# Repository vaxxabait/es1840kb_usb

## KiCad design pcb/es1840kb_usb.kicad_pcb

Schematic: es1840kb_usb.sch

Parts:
C1: 10 µF
C2, C6: 1 µF
C3, C5: 18 pF
C4: 100 nF
DD1: ATMEGA32U2; TQFP32
HL1, HL2, HL3: LED
R1, R2: 22 Ω
R3, R4, R5: 220 Ω
X1: USB
X2: ISP
X3: OLED
XP1: Keyboard
ZQ1: 16 MHz

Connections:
/DBG_RSTn: DD1.24, X2.5 (~RST)
/KB_COL0: DD1.7, XP1.12 (COL_0)
/KB_COL1: DD1.8, XP1.13 (COL_1)
/KB_COL2: DD1.9, XP1.14 (COL_2)
/KB_COL3: DD1.10, XP1.15 (COL_3)
/KB_COL_EN: DD1.6, XP1.21 (COL_EN)
/KB_DAT: DD1.20, XP1.39 (KEY_IN)
/KB_ROW0: DD1.11, XP1.16 (ROW_0)
/KB_ROW1: DD1.12, XP1.17 (ROW_1)
/KB_ROW2: DD1.13, XP1.18 (ROW_2)
/LED_CAPS: DD1.22, R3.2
/LED_EN: DD1.23, XP1.5 (LED_EN)
/LED_LAT: DD1.26, XP1.33 (LED_LAT)
/LED_NUM: DD1.5, XP1.34 (LED_NUM)
/LED_PWR: HL2.2, R4.1
/LED_RUS: DD1.25, XP1.32 (LED_RUS)
/LED_SCRL: DD1.21, R5.2
/OLED_CSn: DD1.14, X3.7 (~CS)
/OLED_DC: DD1.19, X3.6 (D/~C)
/OLED_RSTn: DD1.18, X3.5 (~RES)
/SPI_CLK: DD1.15, X2.3 (SCLK), X3.3 (SCL/SCLK)
/SPI_MISO: DD1.17, X2.1 (MISO)
/SPI_MOSI: DD1.16, X2.4 (MOSI), X3.4 (SDA/MOSI)
/USB_CAP: C6.1, DD1.27
/USB_N: DD1.30, R2.2
/USB_P: DD1.29, R1.2
/XTAL_N: C5.2, DD1.2, ZQ1.2
/XTAL_P: C3.2, DD1.1, ZQ1.1
DGND: C1.2, C2.2, C3.1, C4.1, C5.1, C6.2, DD1.3, DD1.28, R4.2, X1.4 (GND), X2.6 (GND), X3.1 (GND), XP1.20 (GND)
unnamed: R1.1, X1.3 (D+)
unnamed: HL1.2, R3.1
unnamed: HL3.2, R5.1
unnamed: R2.1, X1.2 (D-)
VCC5: C1.1, C2.1, C4.2, DD1.4, DD1.31, DD1.32, HL1.1, HL2.1, HL3.1, X1.1 (VBUS), X2.2 (VCC5), X3.2 (VCC5), XP1.40 (VCC5)

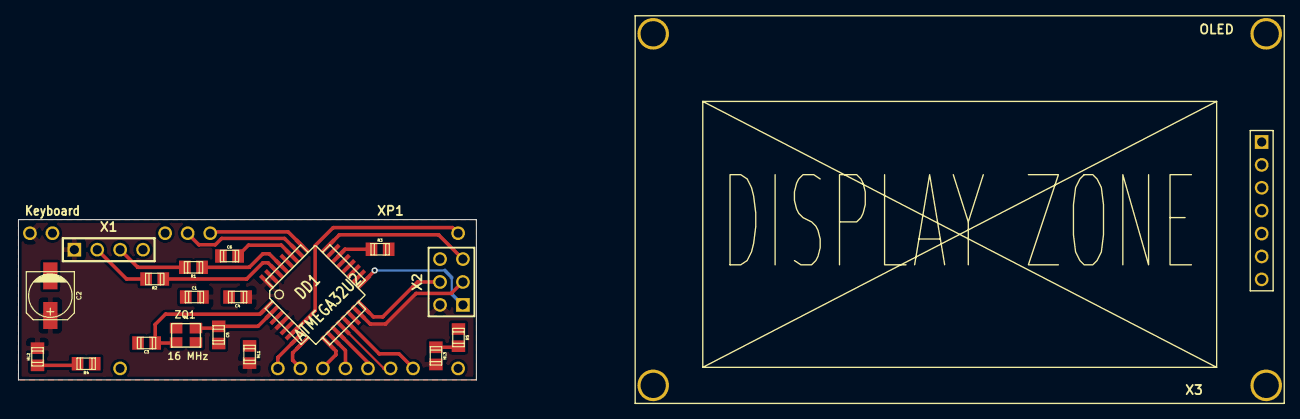
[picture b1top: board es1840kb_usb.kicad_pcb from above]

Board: 2 copper layers, 50.8 x 17.8 mm, 20 parts (0 on the bottom side), 34 nets.

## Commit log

2020-03-04 Move from folders
